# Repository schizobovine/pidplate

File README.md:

pidplate
========

Arduino-ish PID temperature controller for a hotplate based solder reflow-ing thingy.

hardware - Contains the Eagle schematic and board layout
firmware - Arduino sketch & makefile to build code to run it

Bill of materials still TODO, as I haven't really finalized each part, but know
the footprints for each and want to get the board to the fab before I grow old.

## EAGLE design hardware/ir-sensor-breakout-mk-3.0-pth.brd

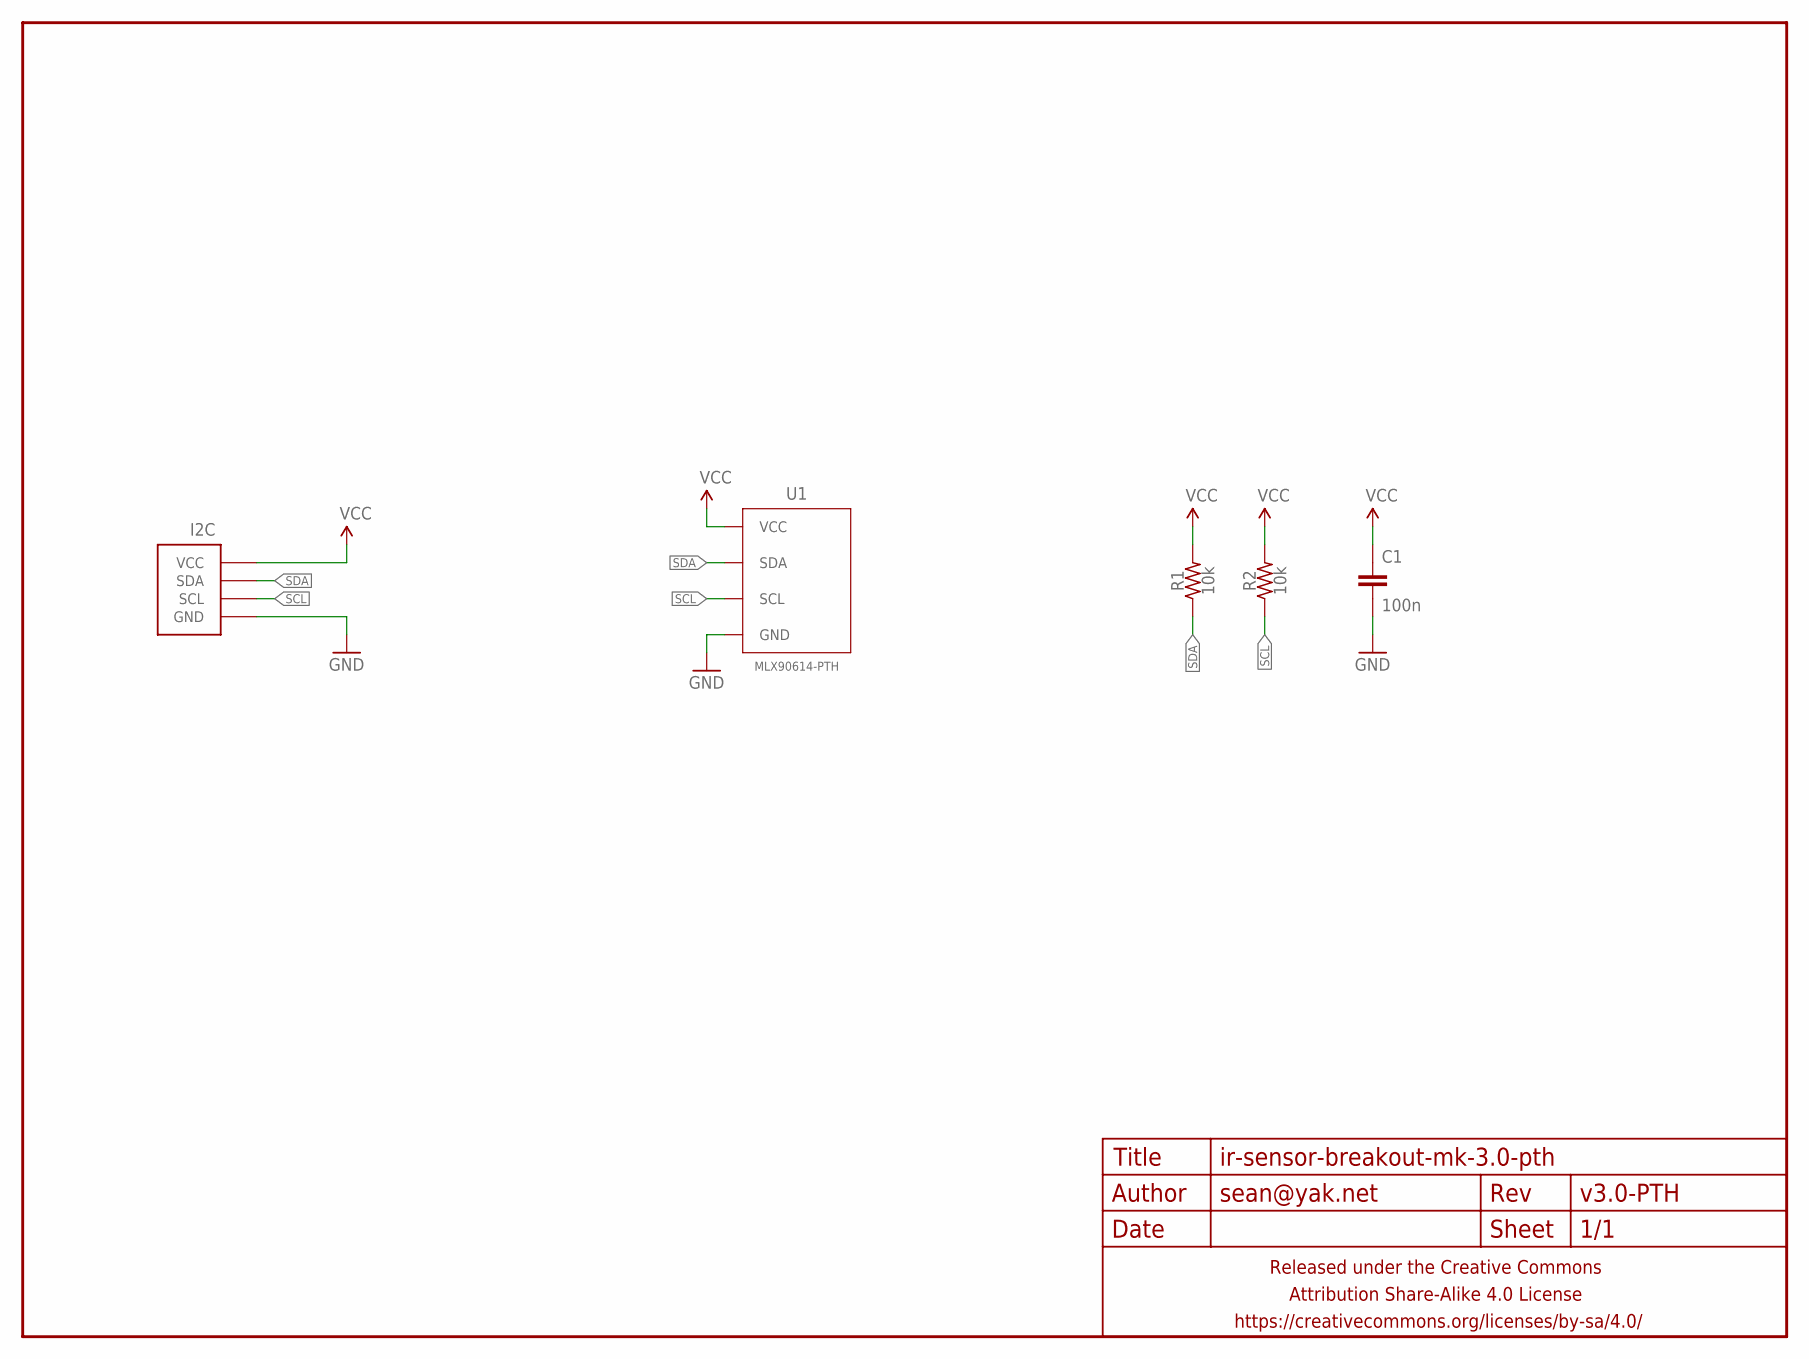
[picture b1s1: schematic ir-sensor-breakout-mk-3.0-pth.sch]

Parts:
C1: 100n; C025-024X044
FRAME1: FRAME-LETTERNO_PACKAGE; DUMMY
I2C: M04-I2CPTH-0.1IN-CENTERED-FLIPPED; 1X04-PTH-VERT-I2C-CENTERED-FLIPPED
R1, R2: 10k; RESISTOR-AXIAL-PTH-5.08MM
U1: MLX90614-PTH; TO-39-4

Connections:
GND: C1.2, I2C.GND, U1.4 (GND)
SCL: I2C.SCL, R2.P$1 (1), U1.1 (SCL)
SDA: I2C.SDA, R1.P$1 (1), U1.2 (SDA)
VCC: C1.1, I2C.VCC, R1.P$2 (2), R2.P$2 (2), U1.3 (VCC)

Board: 2 copper layers, 6 parts (1 on the bottom side), 4 nets, no tracks yet.

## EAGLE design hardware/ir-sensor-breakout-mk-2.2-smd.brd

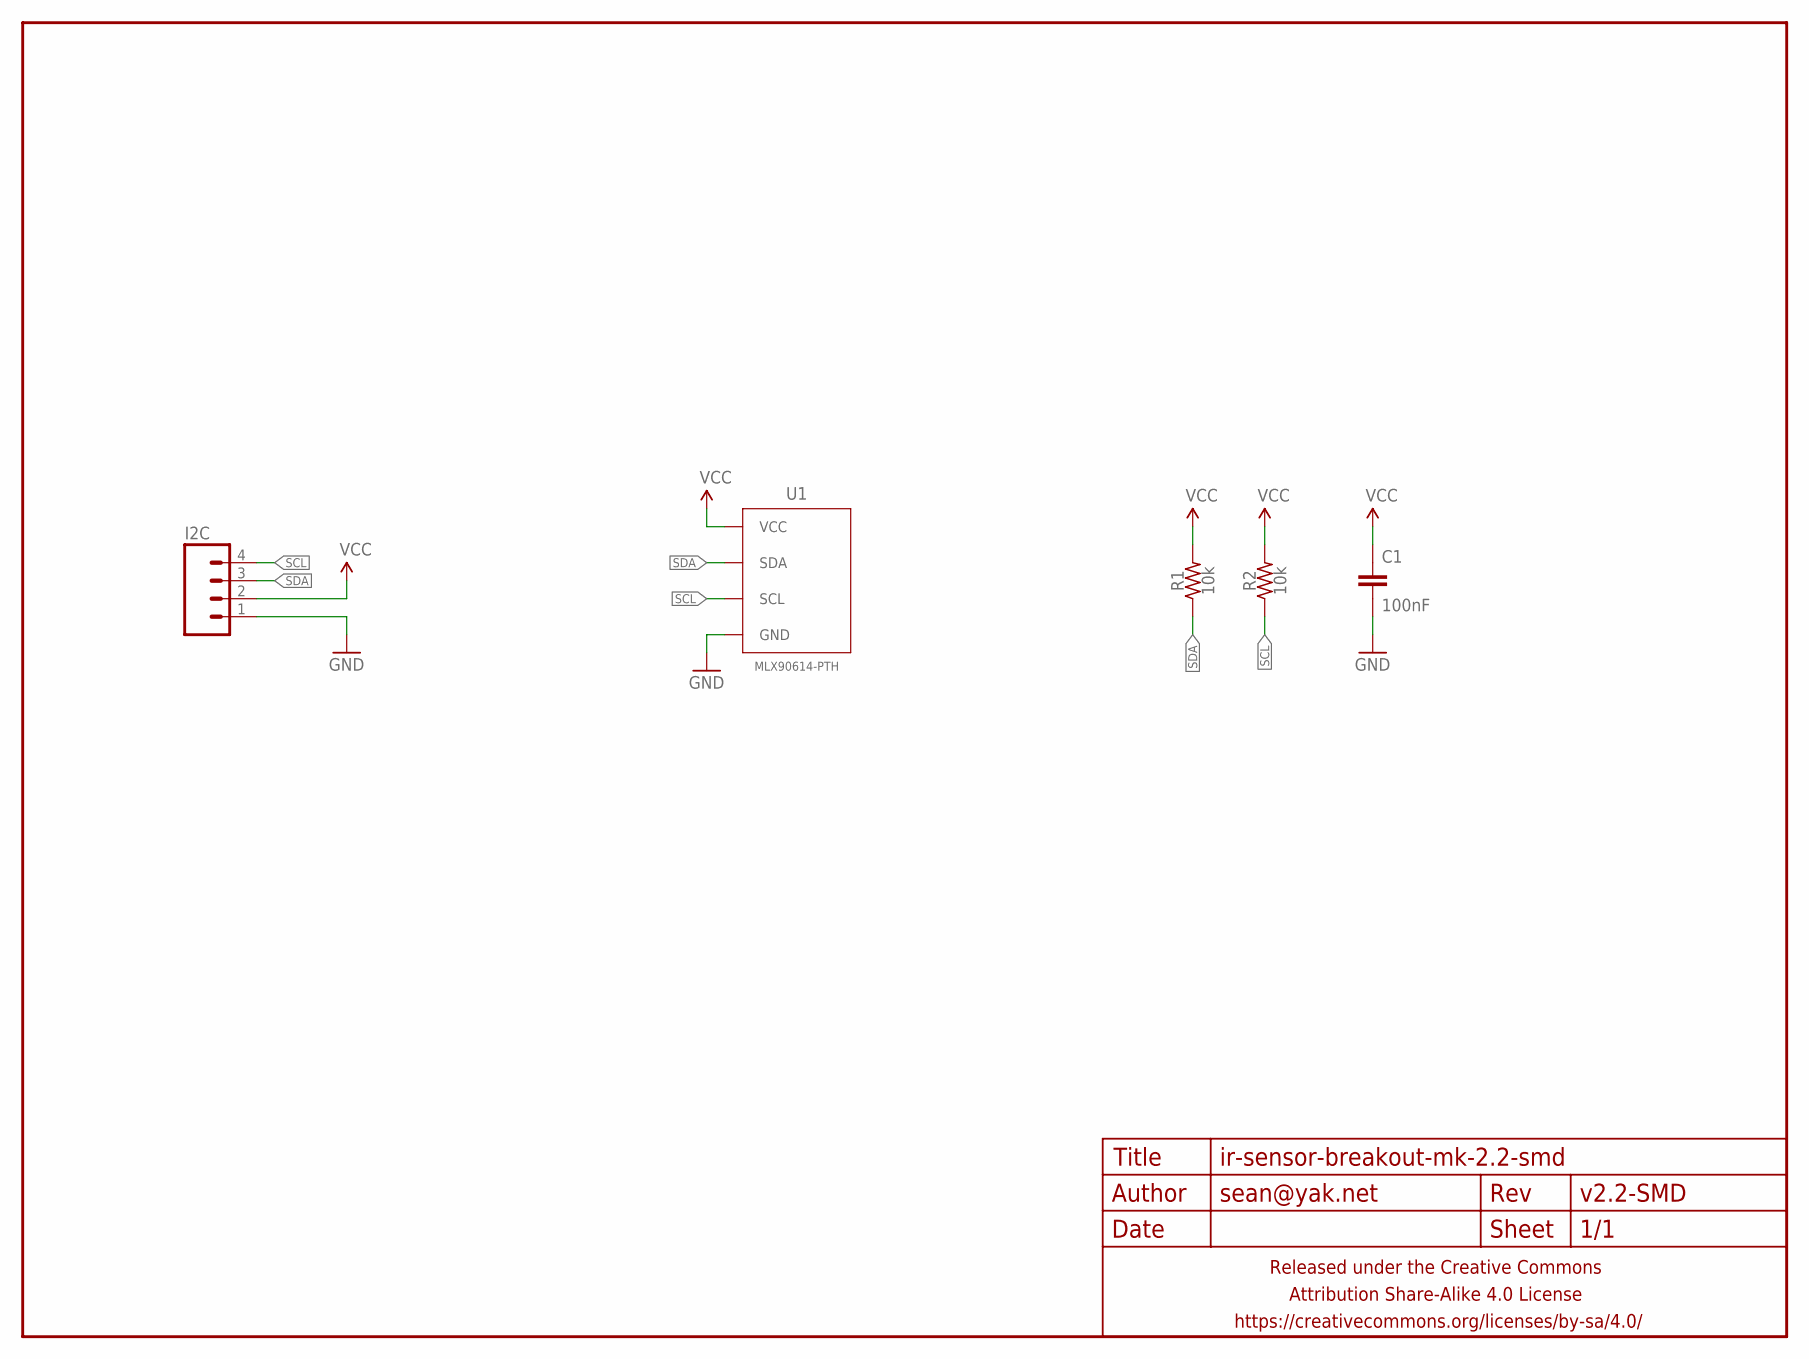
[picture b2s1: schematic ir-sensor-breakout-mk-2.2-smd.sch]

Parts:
C1: 100nF; C0805
FRAME1: FRAME-LETTERNO_PACKAGE; DUMMY
I2C: M04JST-PTH-VERT; JST-4-PH-VERT-PTH
R1, R2: 10k; R0805
U1: MLX90614-PTH; TO-39-4

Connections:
GND: C1.2, I2C.1, U1.4 (GND)
SCL: I2C.4, R2.1, U1.1 (SCL)
SDA: I2C.3, R1.1, U1.2 (SDA)
VCC: C1.1, I2C.2, R1.2, R2.2, U1.3 (VCC)

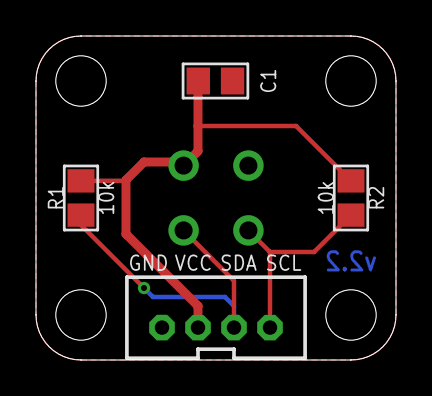
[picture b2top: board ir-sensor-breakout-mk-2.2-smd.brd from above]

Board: 2 copper layers, 20.0 x 18.0 mm, 6 parts (1 on the bottom side), 4 nets.

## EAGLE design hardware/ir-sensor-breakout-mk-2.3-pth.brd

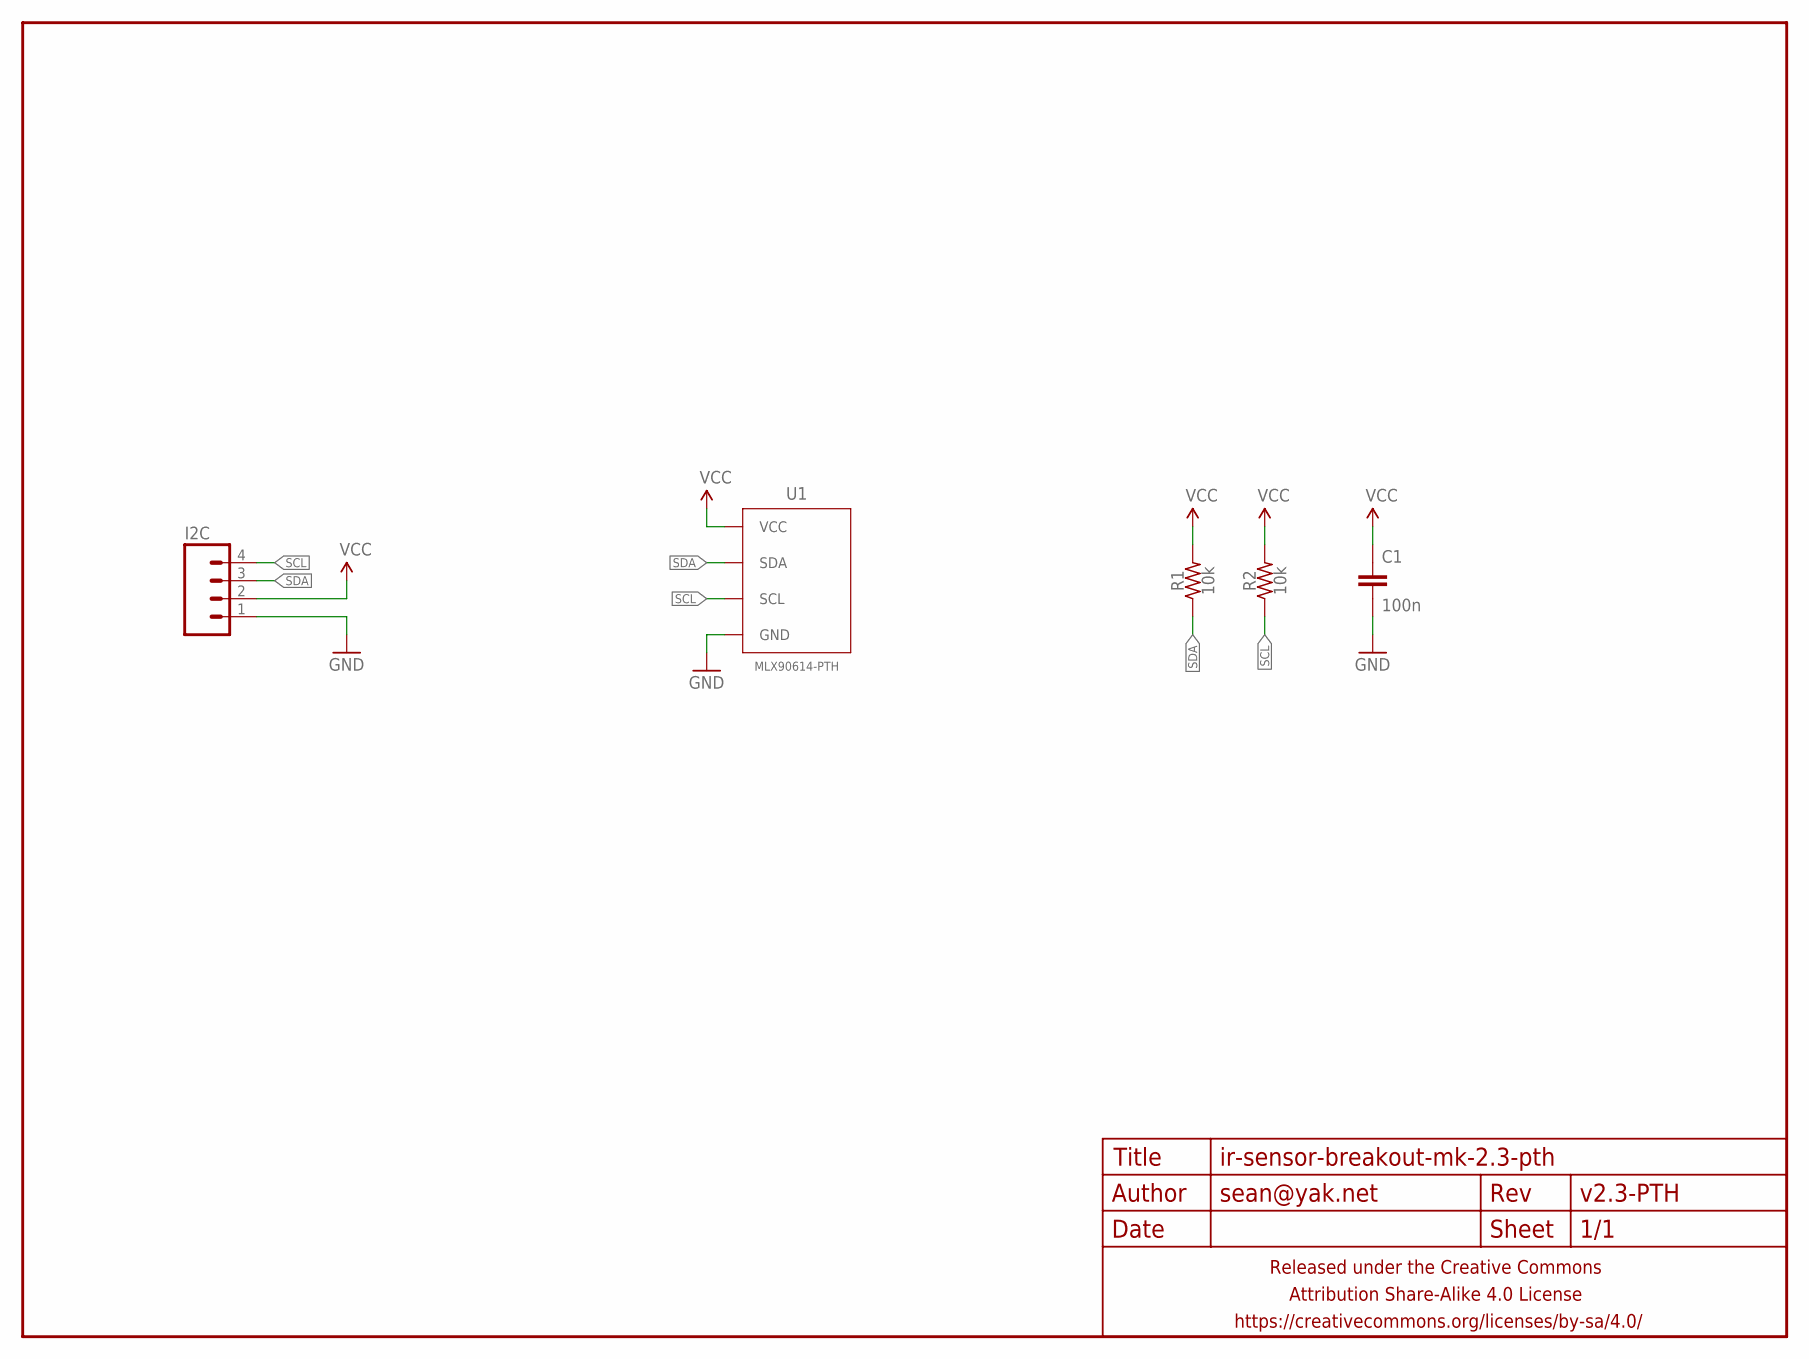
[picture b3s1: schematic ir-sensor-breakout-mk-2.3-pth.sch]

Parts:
C1: 100n; C025-024X044
FRAME1: FRAME-LETTERNO_PACKAGE; DUMMY
I2C: M04JST-PTH-VERT; JST-4-PH-VERT-PTH
R1, R2: 10k; RESISTOR-AXIAL-PTH-5.08MM
U1: MLX90614-PTH; TO-39-4

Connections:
GND: C1.2, I2C.1, U1.4 (GND)
SCL: I2C.4, R2.P$1 (1), U1.1 (SCL)
SDA: I2C.3, R1.P$1 (1), U1.2 (SDA)
VCC: C1.1, I2C.2, R1.P$2 (2), R2.P$2 (2), U1.3 (VCC)

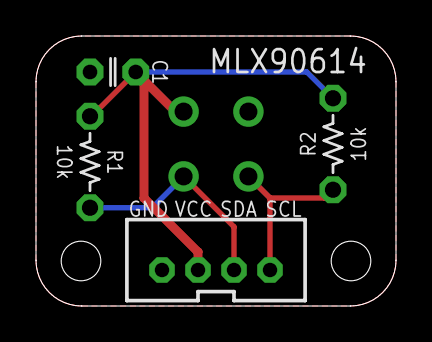
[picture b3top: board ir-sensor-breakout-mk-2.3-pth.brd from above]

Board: 2 copper layers, 20.0 x 15.0 mm, 6 parts (1 on the bottom side), 4 nets.

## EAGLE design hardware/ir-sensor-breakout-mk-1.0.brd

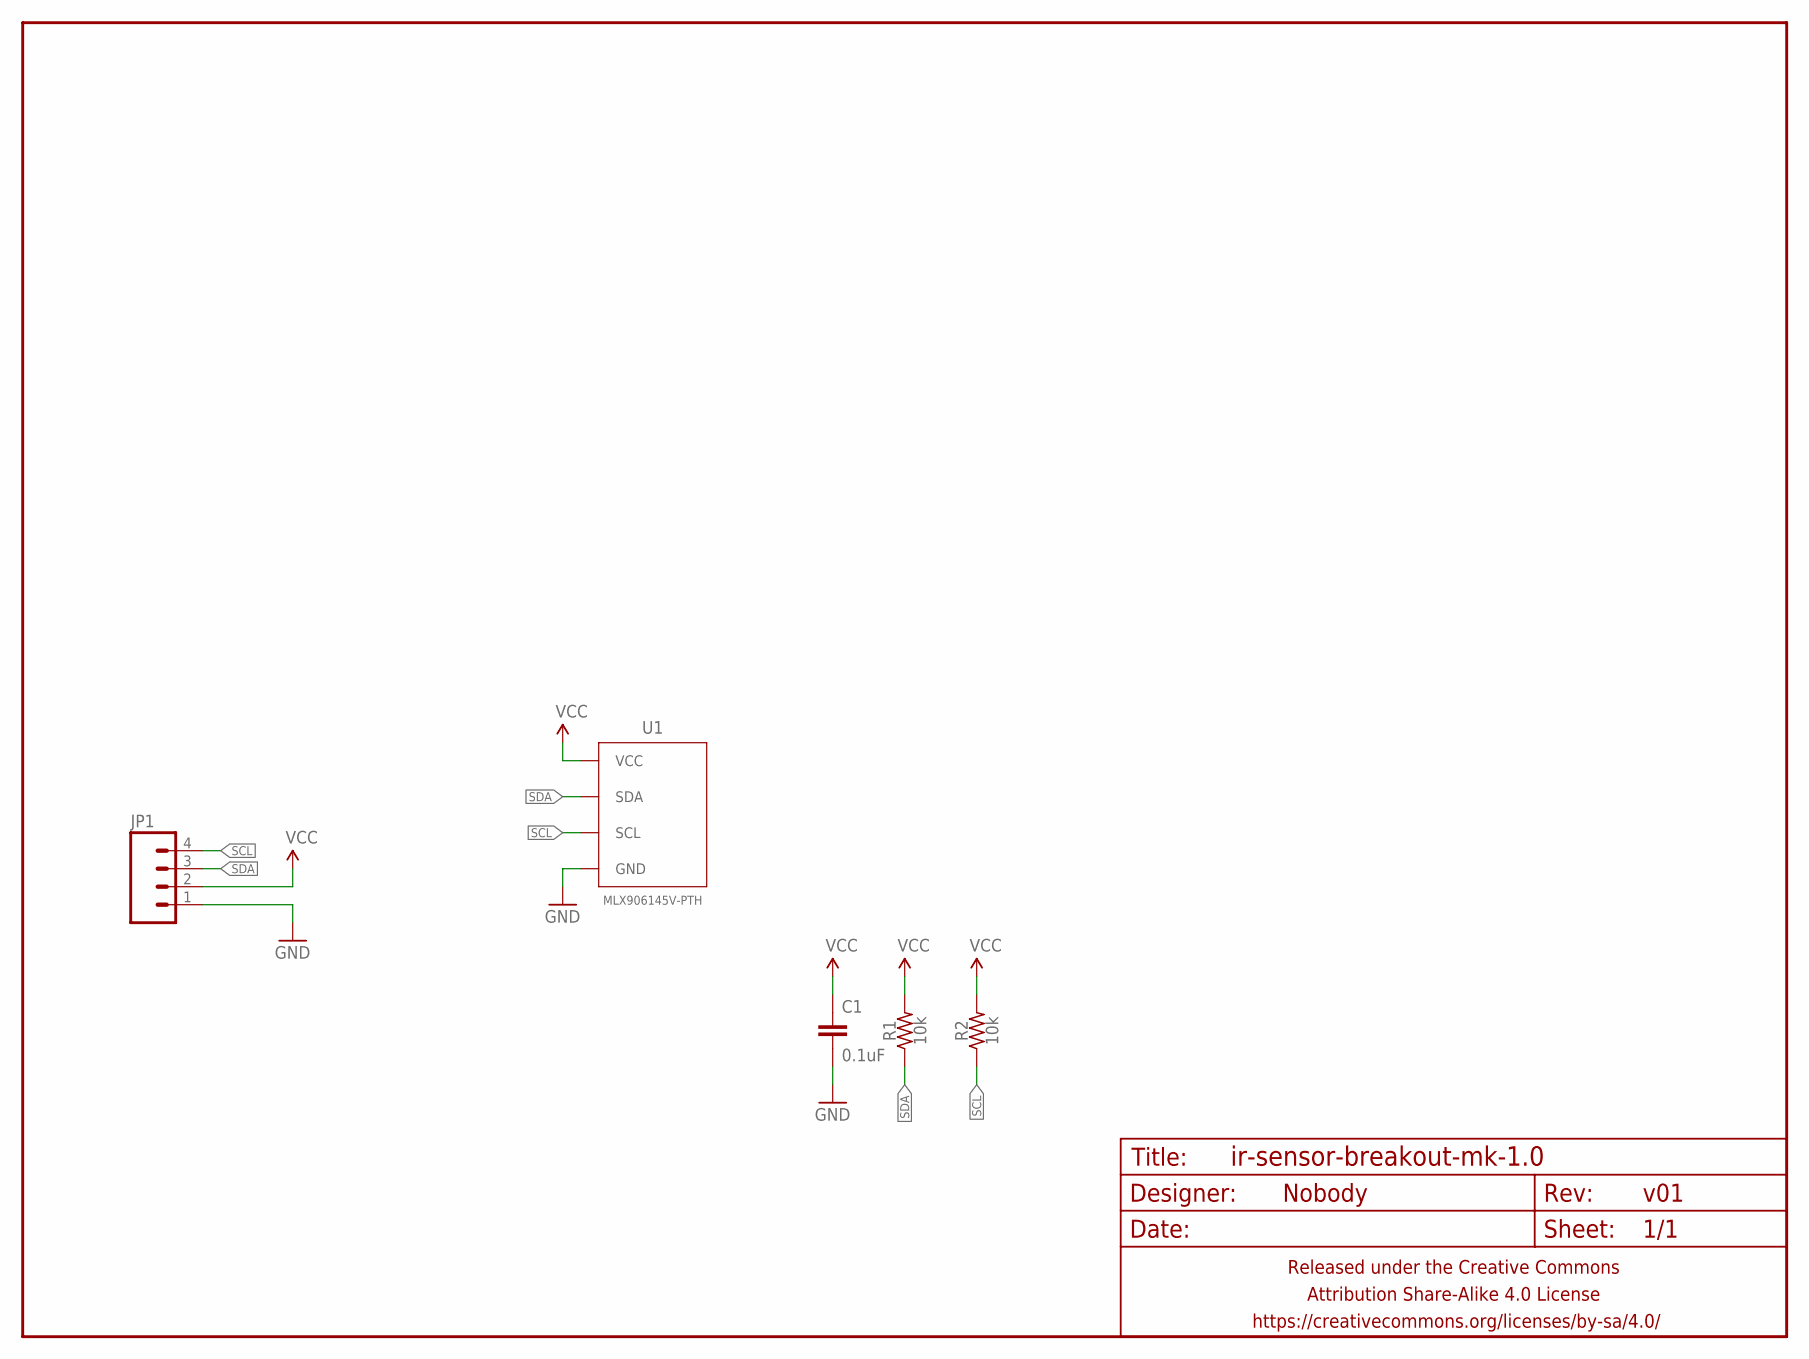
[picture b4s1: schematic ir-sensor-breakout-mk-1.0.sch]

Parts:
C1: 0.1uF; C025-024X044
FRAME1: FRAME-LETTERNO_PACKAGE; DUMMY
JP1: M04JST-PTH; JST-4-PH-RA-PTH
R1, R2: 10k; RESISTOR-AXIAL-PTH-7.62MM
U1: MLX906145V-PTH; TO-39-4

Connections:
GND: C1.2, JP1.1, U1.4 (GND)
SCL: JP1.4, R2.P$1 (1), U1.1 (SCL)
SDA: JP1.3, R1.P$1 (1), U1.2 (SDA)
VCC: C1.1, JP1.2, R1.P$2 (2), R2.P$2 (2), U1.3 (VCC)

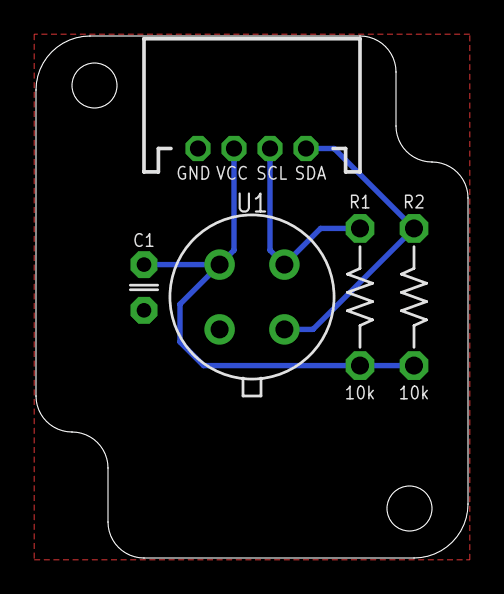
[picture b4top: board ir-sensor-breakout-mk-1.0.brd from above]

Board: 2 copper layers, 24.0 x 29.0 mm, 6 parts (0 on the bottom side), 4 nets.

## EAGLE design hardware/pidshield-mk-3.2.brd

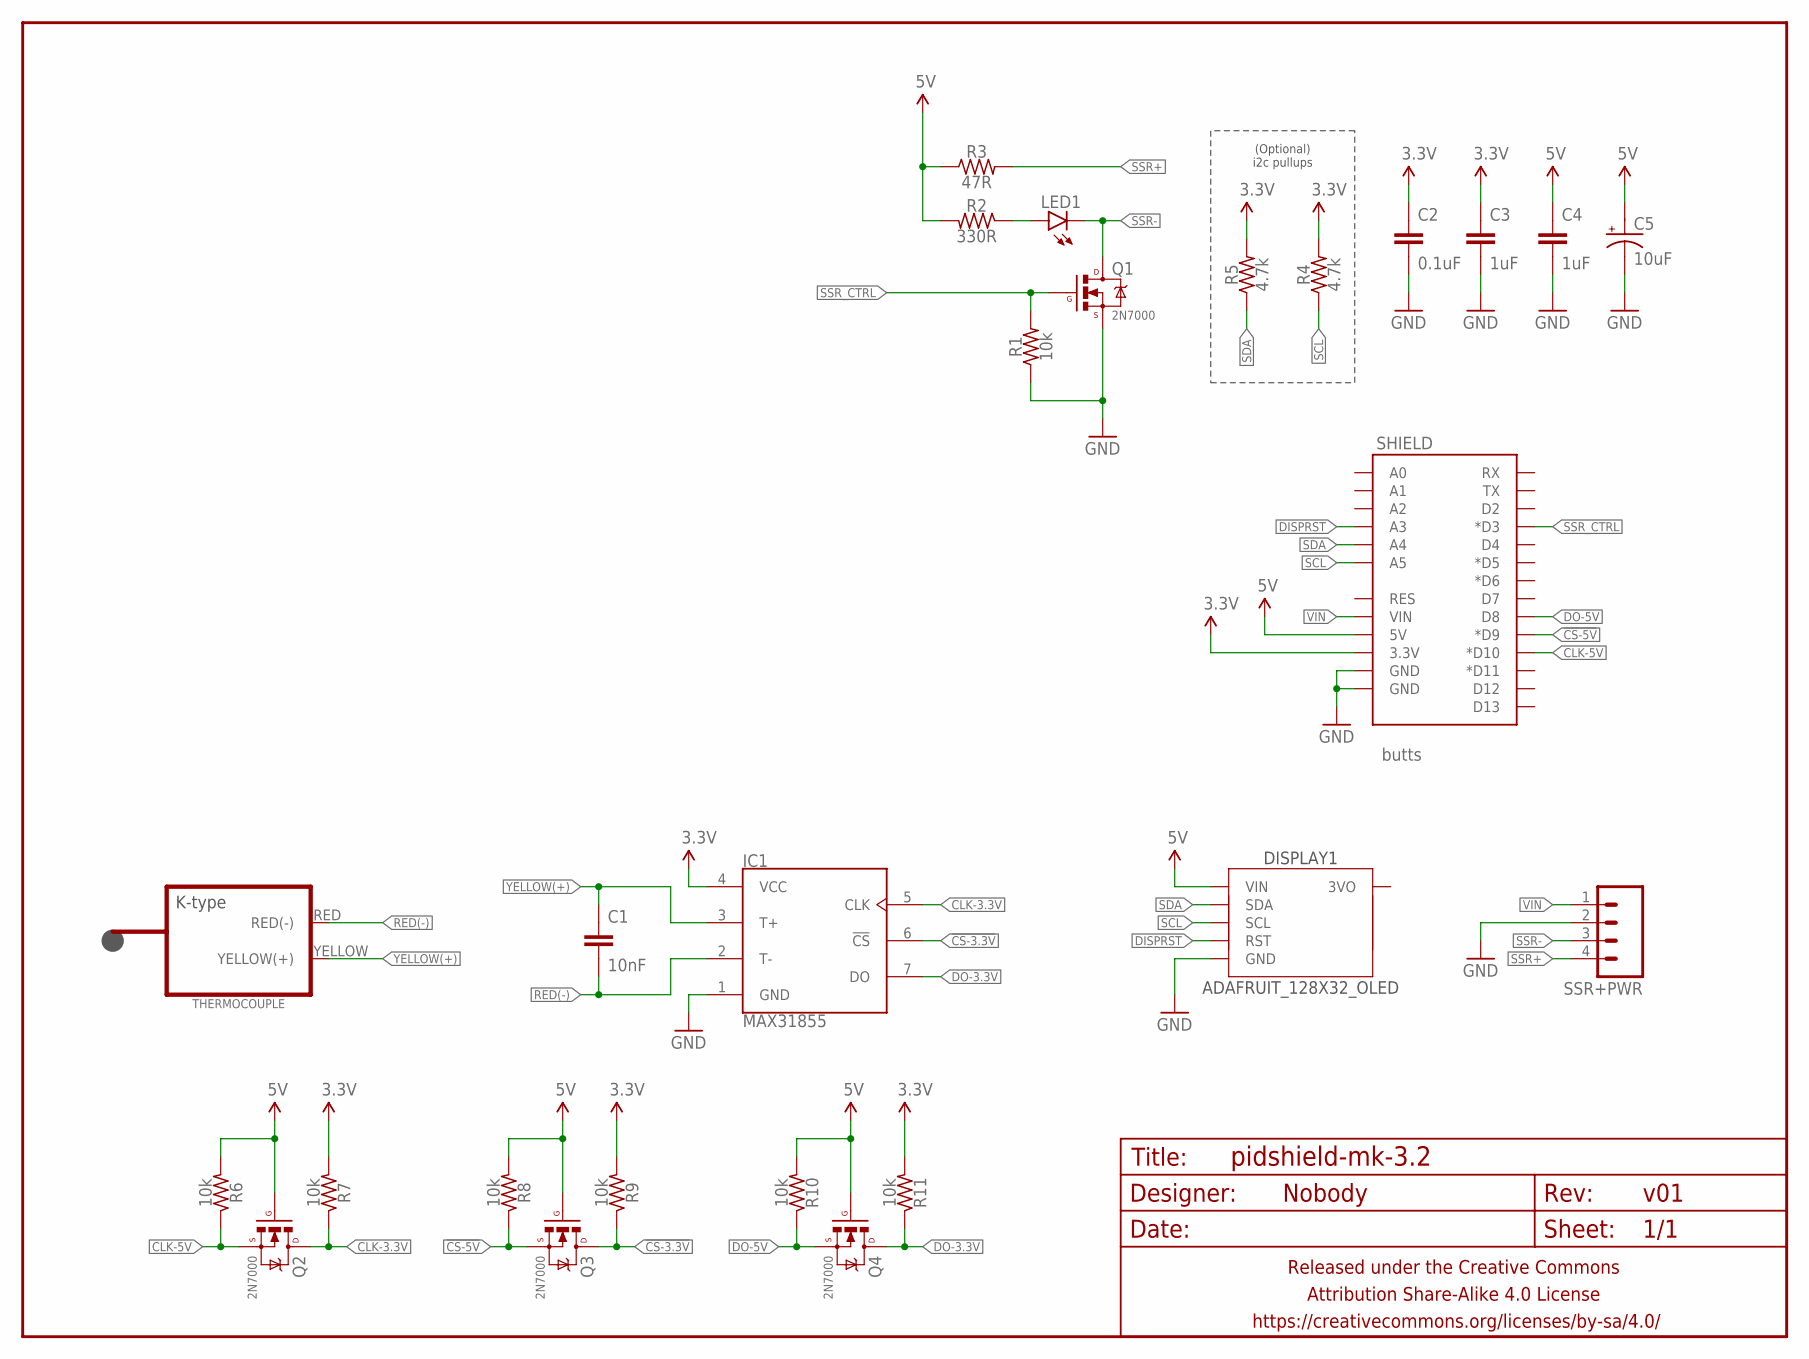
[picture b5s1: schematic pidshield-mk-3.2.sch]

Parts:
C1: 10nF; C0805
C2: 0.1uF; C025-024X044
C3, C4: 1uF; C025-024X044
C5: 10uF; E2,5-6
DISPLAY1: ADAFRUIT_128X32_OLED; ADAFRUIT_128X32_OLED_I2C_CLOSER_NOTITLE
FRAME1: FRAME-LETTERNO_PACKAGE; DUMMY
IC1: MAX31855; SOIC127P600X175-8N
LED1: LED3MM-LESS; LED3MM-LESSSILK
Q1, Q2, Q3, Q4: 2N7000; TO-92-AMMO
R1, R6, R7, R8, R9, R10, R11: 10k; RESISTOR-AXIAL-PTH-7.62MM
R2: 330R; RESISTOR-AXIAL-PTH-7.62MM
R3: 47R; RESISTOR-AXIAL-PTH-7.62MM
R4, R5: 4.7k; RESISTOR-AXIAL-PTH-7.62MM
SHIELD: butts; ARDUINO_SHIELD_SMALLER_NEKKID
SSR+PWR: M04JST_XH_RA; JST-4-XH-RA-PTH
THERMOCOUPLE: THERMOCOUPLE-CONNECTORMINI-PCB; PCC-SMP

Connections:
3.3V: C2.1, C3.1, IC1.4 (VCC), R4.P$2 (2), R5.P$2 (2), R7.P$2 (2), R9.P$2 (2), R11.P$2 (2), SHIELD.3.3V
5V: C4.1, C5.+, DISPLAY1.VIN, Q2.2 (G), Q3.2 (G), Q4.2 (G), R2.P$2 (2), R3.P$1 (1), R6.P$2 (2), R8.P$2 (2), R10.P$2 (2), SHIELD.5V
!CS-3.3V: IC1.6 (!CS), Q3.3 (D), R9.P$1 (1)
!CS-5V: Q3.1 (S), R8.P$1 (1), SHIELD.D9 (*D9)
CLK-3.3V: IC1.5 (CLK), Q2.3 (D), R7.P$1 (1)
CLK-5V: Q2.1 (S), R6.P$1 (1), SHIELD.D10 (*D10)
DISPRST: DISPLAY1.RST, SHIELD.A3
DO-3.3V: IC1.7 (DO), Q4.3 (D), R11.P$1 (1)
DO-5V: Q4.1 (S), R10.P$1 (1), SHIELD.D8
GND: C2.2, C3.2, C4.2, C5.-, DISPLAY1.GND, IC1.1 (GND), Q1.1 (S), R1.P$1 (1), SHIELD.GND@0 (GND), SHIELD.GND@1 (GND), SSR+PWR.2
unnamed: LED1.A, R2.P$1 (1)
RED(-): C1.2, IC1.2 (T-), THERMOCOUPLE.RED (RED(-))
SCL: DISPLAY1.SCL, R4.P$1 (1), SHIELD.A5
SDA: DISPLAY1.SDA, R5.P$1 (1), SHIELD.A4
SSR+: R3.P$2 (2), SSR+PWR.4
SSR-: LED1.K (C), Q1.3 (D), SSR+PWR.3
SSR_CTRL: Q1.2 (G), R1.P$2 (2), SHIELD.D3 (*D3)
VIN: SHIELD.VIN, SSR+PWR.1
YELLOW(+): C1.1, IC1.3 (T+), THERMOCOUPLE.YELLOW (YELLOW(+))

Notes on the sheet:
(Optional) i2c pullups

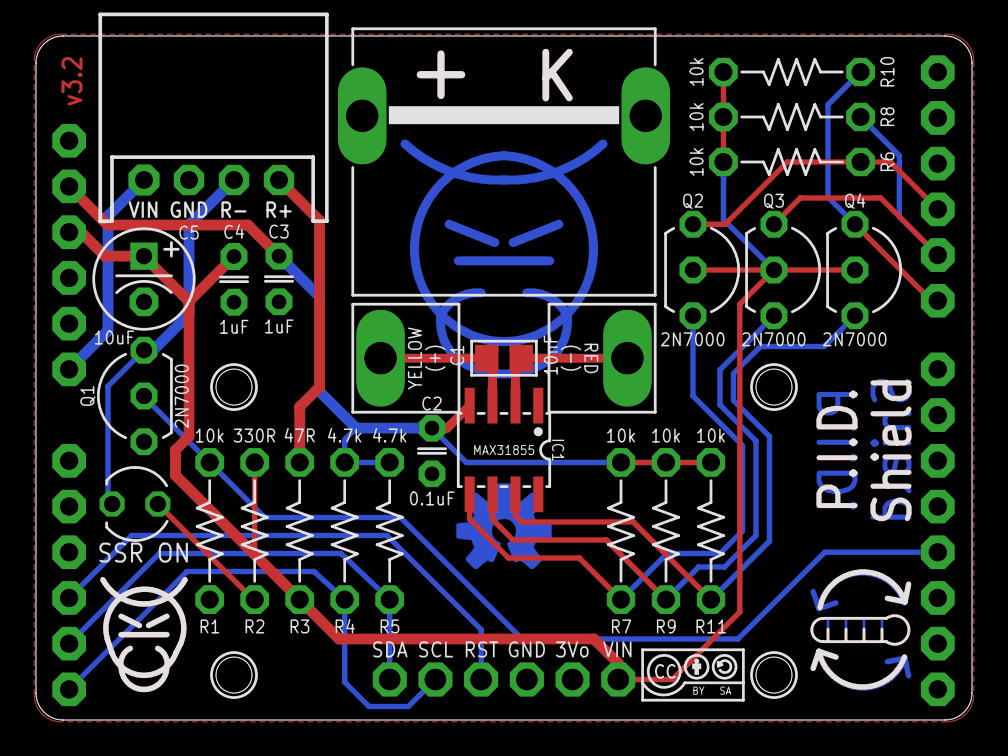
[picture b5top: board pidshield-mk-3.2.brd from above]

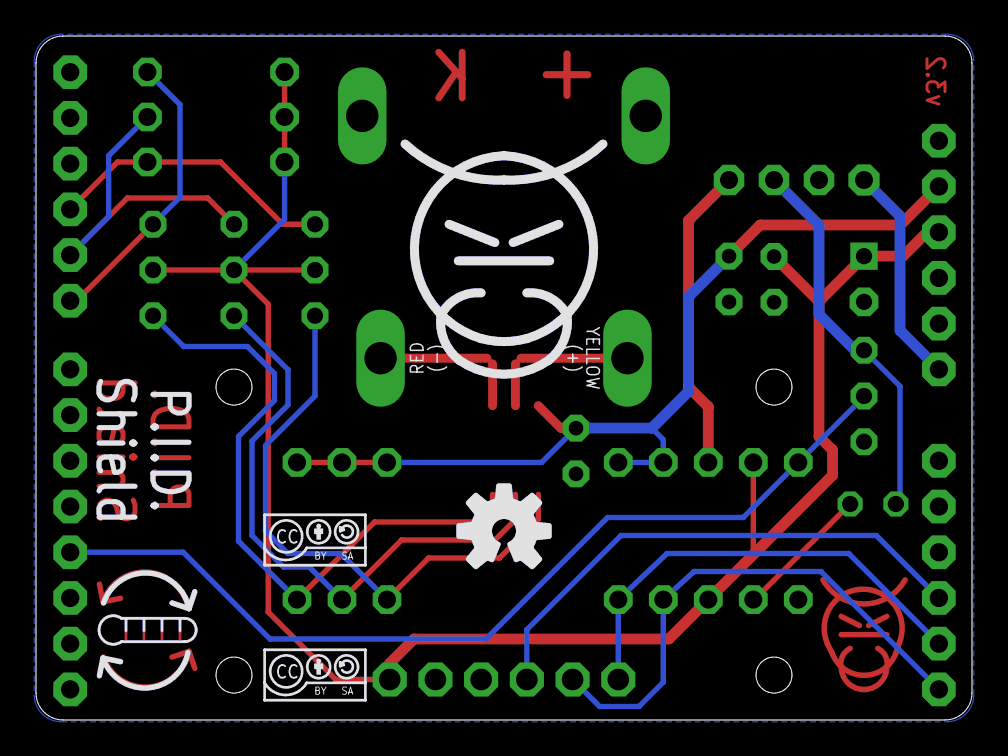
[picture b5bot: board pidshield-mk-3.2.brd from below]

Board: 2 copper layers, 52.0 x 38.0 mm, 35 parts (4 on the bottom side), 19 nets.

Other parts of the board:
U$1: COW_METAL
U$2, U$4, U$5: CC-BY-SA-4.0-NO-URL
U$3, U$6: FEEDBACK3
U$7: OSHWLOGO_BOT_0.2_A
U$8: COW_SMALL_METAL_NOTEXT

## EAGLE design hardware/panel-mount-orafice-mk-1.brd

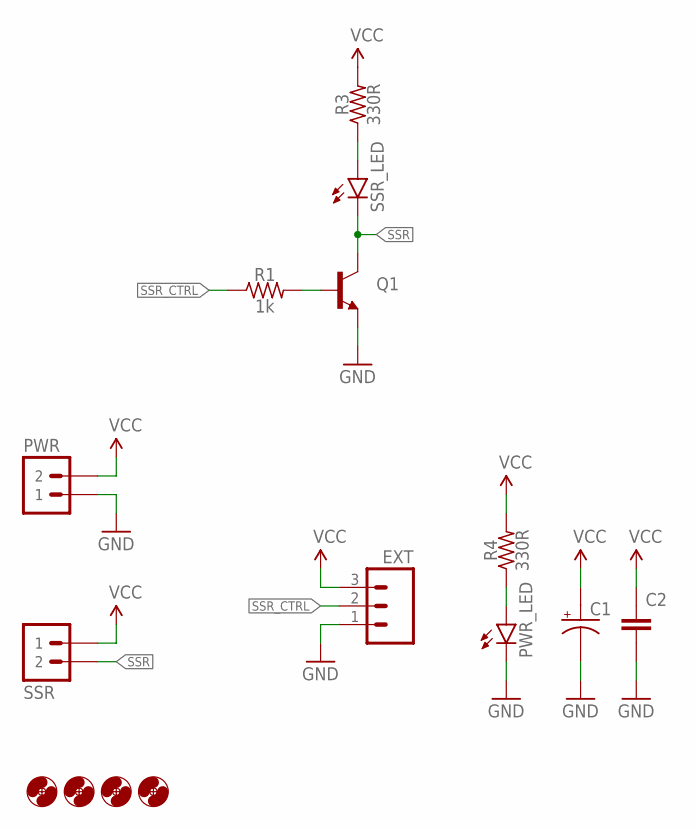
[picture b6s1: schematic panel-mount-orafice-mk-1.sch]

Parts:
C1: CAPACITOR-POLARIZEDE3.5-8; E3,5-8
C2: CAPACITOR-CERAMIC025-024X044; C025-024X044
EXT: M03JST-XH-RA-PTH; JST-3-XH-RA-PTH
H1, H2, H3, H4: HOLE#2; HOLE-#2
PWR: M02JST-PTH-VERT; JST-2-PH-VERT-PTH
PWR_LED: LED3MM
Q1: TRANSISTOR_NPNTO-92-AMMO-EBC; TO-92-AMMO
R1: 1k; RESISTOR-AXIAL-PTH-6.35MM
R3, R4: 330R; RESISTOR-AXIAL-PTH-6.35MM
SSR: M02JST-PTH-VERT; JST-2-PH-VERT-PTH
SSR_LED: LED3MM

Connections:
GND: C1.-, C2.2, EXT.1, PWR.1, PWR_LED.K (C), Q1.1 (E)
unnamed: Q1.2 (B), R1.P$2 (2)
unnamed: R3.P$1 (1), SSR_LED.A
unnamed: PWR_LED.A, R4.P$1 (1)
SSR: Q1.3 (C), SSR.2, SSR_LED.K (C)
SSR_CTRL: EXT.2, R1.P$1 (1)
VCC: C1.+, C2.1, EXT.3, PWR.2, R3.P$2 (2), R4.P$2 (2), SSR.1

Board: 2 copper layers, 15 parts (0 on the bottom side), 7 nets, no tracks yet.

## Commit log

2014-11-18 Finally getting this bastard into source control. Bad programmer, I know. :P
2014-11-18 words words words (to the README)
2014-11-21 updating license to GPL (for code); eagle files will be CC4.0-by-sa; gitignore to be combo of C and eagle stuff
2014-12-11 misc changes upon receiving boards, and some work maybe on the firmware
2014-12-11 ignoring build dir
2014-12-12 revision dos will use 3.3V power to make life easier
2014-12-12 twiddling code bits
2014-12-12 now 50x50mm, reduced components, relatively happy with layout
2014-12-14 mini mini mini
2014-12-15 more tweaks to standalone; new shield-based version
2014-12-15 think i've got the layout how i want it
2014-12-21 new shield for 3.3V boards only, so no need for a crapload of MOSFETs
2014-12-28 in progress commit
2014-12-28 switchover to using 7seg display b/c fuck LCDs
2015-01-09 alkdfjasdj
2015-05-11 complete relayout of PTH shield to use a tiny OLED display from Adafruit
2015-05-11 originally to mount a connector to the outside of the case
2015-05-11 breakout for Melexis IR temp sensor for future version
2015-05-23 firmware dir reorg to accomodate host-side simulator harness
2015-05-23 recursify build dir ignore
2015-06-14 modifying to work with OLED display instead of crappy LCD
2015-06-14 new revision swap BJT for FET and add appropriate pullup
2015-06-22 not sure what i was going to do with this
2015-06-22 firmware work
2015-06-22 simple command line simulator to dump out a CSV for analysis
2015-06-22 changes to make controller work both in arduino land and on the Linux CLI
2015-06-23 simulator work, adding in auto-termination if the run looks stable
2015-06-24 tweaks to simulator and ignore list
2015-06-24 simulator tweaks to use command line args
2015-06-27 adding serial logging to get temp data
2015-06-27 twiddling around with IR sensor breakouts
2015-06-27 data logger sketch for plate
2015-06-28 some python utils to gather/visualize the data
2015-06-28 fiddling with the pth breakout
2015-06-28 improved serial data logging (i.e., it's usable now)
2015-06-29 graphing sucks. why didn't i use a spreadsheet?
2015-06-29 removing some dead-ends/boards not going to be fabbed
2015-10-21 descriptions in markdown as used on oshpark
2016-05-23 new IR thermometer breakouts
2016-05-24 tinier version

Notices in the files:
parts and their libraries:
A_butts: Released under the Creative Commons Attribution Share-Alike 4.0 License
A_butts: https://creativecommons.org/licenses/by-sa/4.0
A_butts: Released under the Creative Commons
